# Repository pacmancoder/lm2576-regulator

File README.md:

# hw-lm2576-regulator
lm2576-based low-ripple 5V regulator supply

### 3D overview

### Circuit

### Pcb

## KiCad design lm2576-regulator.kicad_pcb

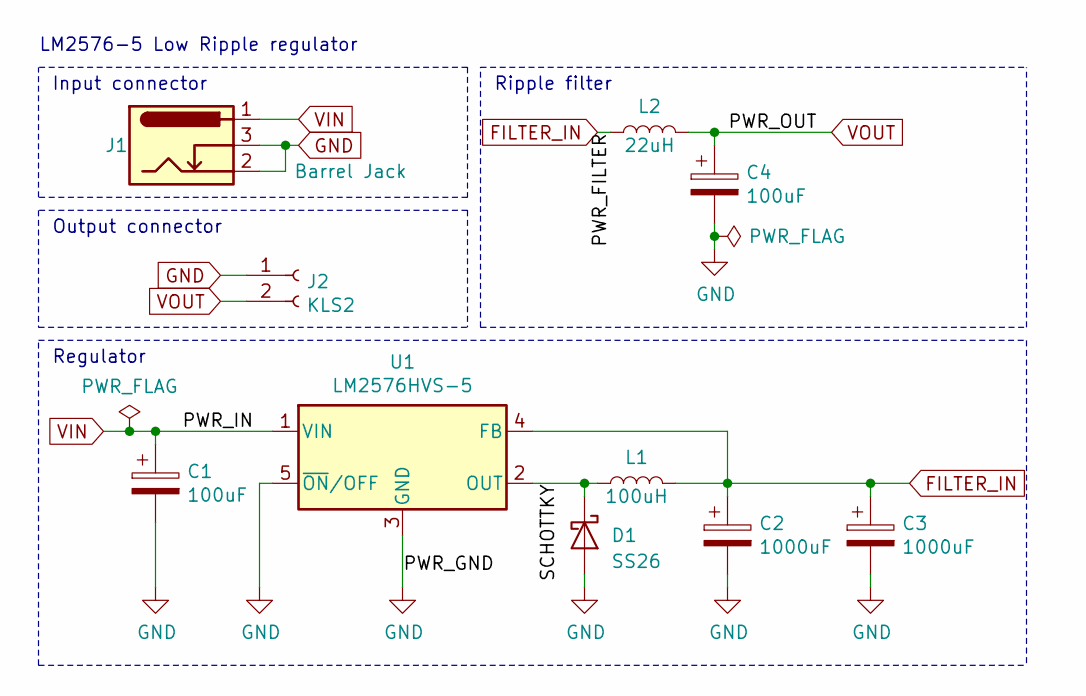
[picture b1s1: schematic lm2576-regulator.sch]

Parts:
C1, C4: 100uF; CP_Elec_8x10
C2, C3: 1000uF; CP_Elec_10x10.5
D1: SS26; D_SMC
J1: Barrel Jack; BarrelJack_Wuerth_6941xx301002
J2: KLS2; TerminalBlock_MetzConnect_Type055_RT01502HDWU_1x02_P5.00mm_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
L1: 100uH; L_12x12mm_H8mm
L2: 22uH; L_12x12mm_H8mm
U1: LM2576HVS-5; TO-263-5_TabPin3

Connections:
/SCHOTTKY: D1.1 (K), L1.1, U1.2 (OUT)
FILTER_IN: C2.1, C3.1, L1.2, L2.1, U1.4 (FB)
GND: C1.2, C2.2, C3.2, C4.2, D1.2 (A), J1.2, J1.3, J2.1, U1.3 (GND), U1.5 (~ON~/OFF)
VIN: C1.1, J1.1, U1.1 (VIN)
VOUT: C4.1, J2.2, L2.2

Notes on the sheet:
Regulator
Ripple filter
Output connector
Input connector
LM2576-5 Low Ripple regulator

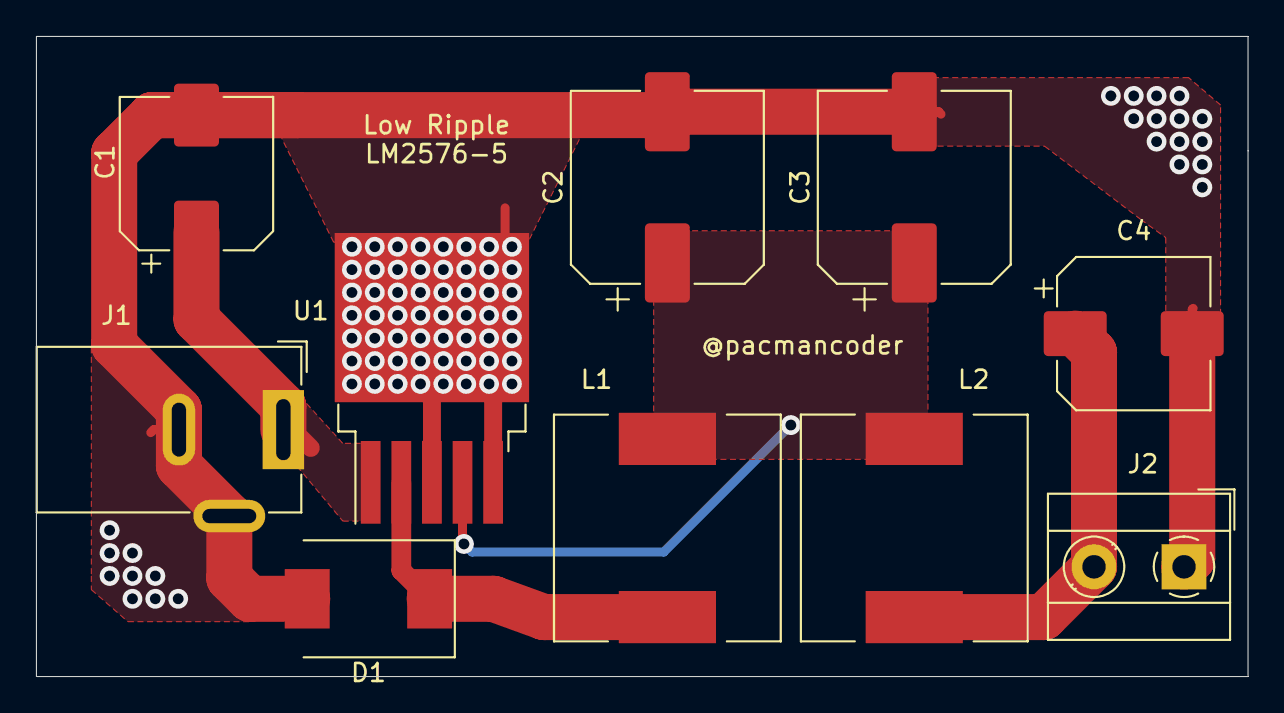
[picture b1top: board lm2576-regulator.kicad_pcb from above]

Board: 2 copper layers, 67.3 x 35.6 mm, 10 parts (0 on the bottom side), 5 nets.

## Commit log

2020-01-30 Added MIT license file
2020-02-05 Initial desing of the converter
2020-02-05 Made improvements for production on a factory
2020-02-08 Modified after review of Alexander
2020-02-08 Added product images
